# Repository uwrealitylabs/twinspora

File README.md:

# twin28xx

Twin DRV8316 motor drivers controlled by an STM32G473 with an onboard MT6701 magnetic encoder for each motor. Sized to fit two iPOWER GM2804 / Cubemars GL-30 motors on the back of the PCB.

## Specs

- **MCU:** STM32G473
- **Motor drivers:** 2× DRV8316CR (Controlled via SPI)
- **Encoder:** MT6701 onboard. Optional SPI breakout for remotely-mounted motors — desolder 3× 0603 resistors to disconnect onboard sensor & use "JST" SH-1.0 6 pin header.
- **Connectivity:** CAN-FD, USB 2.0, I²C

## Power & decoupling

- 2x B2B (BK22C07-4DP/2-0.4V) for power input + CAN. In the future there will be alternate versions with screw terminal & XT-30. 
- Reverse-polarity protection on the supply input
- 2× 330 µF electrolytic bulk caps
- 12× 0805 ceramic footprints (6 per driver) for additional decoupling

## Protection

- ESD protection on every external connector

## Configuration

- 2.54mm through hole headers for CAN bus termination and I²C pull-ups

Inspired by/references:
- microspora: https://oshwlab.com/the.skuric/microspora-simplefoc-antun
- Lemon Pepper Stepper: https://github.com/VIPQualityPost/lemon-pepper-stepper

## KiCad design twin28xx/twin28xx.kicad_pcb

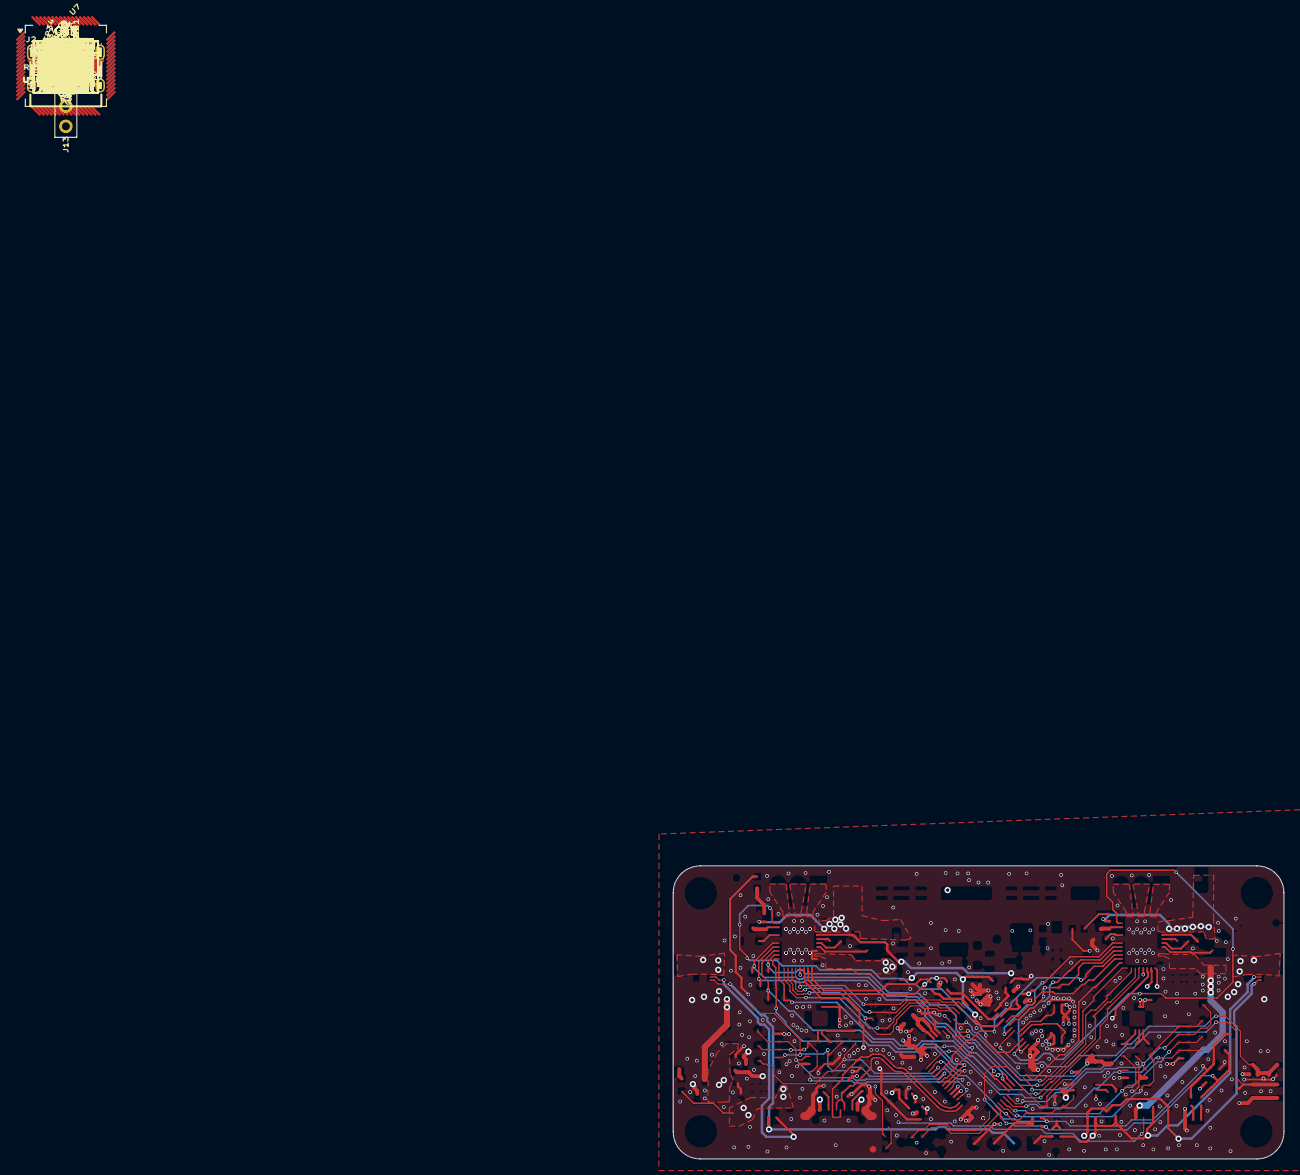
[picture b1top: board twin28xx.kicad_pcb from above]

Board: 4 copper layers, 76.9 x 36.9 mm, 201 parts (0 on the bottom side), 111 nets.

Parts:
C1, C2: 0402CG470J500NT; C_0402_1005Metric
C3, C4, C6, C16, C19, C20, C21, C22, C23, C25, C27, C36, C50, C59, C60: CL05B104KB54PNC; C_0402_1005Metric
C5, C26, C28, C29: CL05A105KA5NQNC; C_0402_1005Metric
C7, C8, C34, C35, C37, C48, C49, C51: GRM21BR61H106KE43L; C_0805_2012Metric
C9, C10, C12, C13, C15, C17, C30: CL05B103KB5NNNC; C_0402_1005Metric
C11, C18: 0402CG300J500NT; C_0402_1005Metric
C14, C24: CL10A475KO8NNNC; C_0603_1608Metric
C31, C33, C45, C47: CL10A105KB8NNNC; C_0603_1608Metric
C32, C46: CL10B473KB8NNNC; C_0603_1608Metric
C38, C39, C40, C41, C42, C43: VHXC0581V101MVCG; CP_Elec_6.3x5.8
D1, D2: 1N4148WS_T4; D_SOD-323_HandSoldering
D3, D4: BZT52B5V1S_C19077434; D_SOD-323_HandSoldering
FID1, FID2, FID3: Fiducial; Fiducial_0.5mm_Mask1mm
H1, H4, H7, H10: MountingHole_Pad; MountingHole_3.2mm_M3_Pad_Via
H2, H5, H8, H11: MountingHole_Pad; MountingHole_2.2mm_M2_DIN965_Pad
H3, H6, H9, H12: SMTSOM225BTR; SMD_BD5.6-D3.6
J1, J7, J8: XY-SH1_0-3A61; CONN-SMD_3P-P1.00_XYECONN_XY-SH1.0-3A61
J2: TYPE-C-31-M-12; USB-C_SMD-TYPE-C-31-M-12_1
J3: Tag-Connect_TC2030-IDC-NL_2x03_P1.27mm_Vertical
J4: DB125-2_54-2P-GN__mirror; CONN-TH_DB125-2.54-2P-GN__mirror
J5: XY-SH1_0-4A61; CONN-SMD_4P-P1.00_XYECONN_XY-SH1.0-4A61
J6: DB125-2_54-2P-GN; CONN-TH_DB125-2.54-2P-GN
J9, J10: Conn_01x03; CONN-TH_DB125-2.54-3P-GN
J11, J12: XY-SH1_0-6A51; CONN-SMD_6P-P1.00_XY-SH1.0-6A51
J13: Conn_01x04; PinHeader_1x04_P2.54mm_Vertical
L1, L2: PRS3015-470MT; IND-SMD_L3.0-W3.0_PRS3015
L3: GZ1608D601TF; L_0603_1608Metric
LED1, LED2: KT-0603W; LED0603-R-RD_WHITE
LED3, LED4, LED5: KT-0603R; LED0603-RD
Q1: AO3401A; SOT-23
R1, R4, R7, R11, R22, R26: 0402WGF1002TCE; R_0402_1005Metric
R2, R3, R5, R6, R18, R40: 0402WGF5101TCE; R_0402_1005Metric
R8, R9, R10, R30, R39: 0402WGF3300TCE; R_0402_1005Metric
R12, R13, R14, R17, R19, R20: 0402WGF499JTCE; R_0402_1005Metric
R15, R16, R21: 0402WGF1200TCE; R_0402_1005Metric
R23, R24, R31, R32, R33, R34, R36, R37, R38: 0603WAF0000T5E; R_0603_1608Metric
R25, R29, R35: 0402WGF1003TCE; R_0402_1005Metric
R27, R28: 0402WGF604JTCE; R_0402_1005Metric
SW1, SW2: SKSGPAE010; SW-SMD_SKSGAAE010
TP1, TP2, TP3, TP4, TP5, TP6, TP7, TP8, TP9, TP10, TP11, TP12, TP13, TP14, TP15, TP16, TP17, TP18, TP19, TP20, TP21, TP22, TP23, TP24, TP25, TP26, TP27, TP28, TP29, TP30, TP31, TP32, TP33, TP34, TP35, TP36, TP37, TP38, TP39, TP40, TP41, TP42, TP43, TP44, TP45, TP46: TestPoint_Pad_D1.0mm
U1, U2: BK22C07-4DP/2-0_4V(800); CONN-SMD_4P-P0.40_BAM04-08073-0414
U3: FMMT620TA; SOT-23-3_L2.9-W1.6-P1.90-LS2.8-BR
U4: WSD4066DN; DFN-8_L3.2-W3.1-P0.65-LS3.4-BL-EP
U5: SMF30A_C19077518; SOD-123FL_L2.7-W1.8-LS3.8
U6, U10, U17, U19: SRV05-4A; SOT-23-6
U7: STM32G473RBTx; LQFP-64_10x10mm_P0.5mm
U8: TPD1E10B06DPYR; DFN1006-2L-BI
U9: XC6206P332MR; SOT-23-3_L2.9-W1.6-P1.90-LS2.8-BR
U11: CA-IF1044VD-Q1; DFN-8_L3.0-W3.0-P0.65-BL-EP2.45
U12: ACT1210D-101-2P-TL00; FILTER-SMD_4P-L3.2-W2.5-BL_ACT1210D-101-2P-TL00
U13: PESD2CAN; SOT-23-3_L2.9-W1.3-P1.90-LS2.4-BR
U14, U15: DRV8316CRRGFR; VQFN-40_L7.0-W5.0-P0.50-BL-EP5.7
U16, U18: MT6701QT; QFN-16-1EP_3x3mm_P0.5mm_EP1.7x1.7mm
X1: X322512MSB4SI

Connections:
+3.3V: C6.2, C7.1, C8.1, C20.1, C21.1, C22.1, C23.1, C24.1, C59.2, C60.2, J5.2, J11.2, J12.2, J13.4, L3.2, LED2.1 (A), LED4.2 (A), LED5.2 (A), R7.2, R34.2, SW1.1, SW1.3, TP25.1 (1_1), U7.1 (VBAT), U7.16 (VDD), U7.32 (VDD), U7.48 (VDD), U7.64 (VDD), U9.3 (Vout), U10.5 (VP), U14.37 (VREF/ILIM), U15.37 (VREF/ILIM), U16.13 (VDD), U16.14 (MODE), U17.5 (VP), U18.13 (VDD), U18.14 (MODE), U19.5 (VP)
+5V: C4.2, C5.2, C14.2, C16.2, D2.1 (K), Q1.2 (S), TP26.1 (1_1), U8.2, U9.2 (Vin), U11.3 (VCC)
+BATT: D1.1 (K), J4.2, J6.2, U1.5, U1.6, U1.9, U1.10, U2.5, U2.6, U2.9, U2.10, U4.1 (S1), U4.3 (S2)
/5V_BKOUT: C34.1, C35.1, J1.2, L1.1, U14.3 (FB_BK)
/ADC1_IN3: C9.2, R12.1, U7.14 (PA2)
/ADC1_IN4: C13.2, R17.1, U7.17 (PA3)
/ADC2_IN1: C10.2, R13.1, U7.12 (PA0)
/ADC2_IN2: C15.2, R19.1, U7.13 (PA1)
/ADC5_IN1: C12.2, R14.1, U7.42 (PA8)
/ADC5_IN2: C17.2, R20.1, U7.43 (PA9)
/BOOT: R6.2, SW1.2, SW1.4, U7.61 (PB8)
/BUCK: C48.1, C49.1, L2.1, Q1.3 (D), TP45.1 (1_1), U15.3 (FB_BK)
/CAN_H: J7.3, J8.3, R21.2, R23.2, R28.2, U1.4, U2.4, U12.4, U13.1
/CAN_L: J7.2, J8.2, J13.2, R24.2, U1.3, U2.3, U12.3, U13.2
/CAN_VIO: C19.2, R22.2, TP43.1 (1_1), U7.22 (PC4), U11.5 (VIO/NC)
/CC1: J2.A5 (CC1), R2.1
/CC2: J2.B5 (CC2), R3.1
/D+: C2.2, J2.A6 (DP1), J2.B6 (DP2), U6.1 (IO1), U6.6 (IO4), U7.46 (PA12)
/D-: C1.2, J2.A7 (DN1), J2.B7 (DN2), U6.3 (IO2), U6.4 (IO3), U7.45 (PA11)
/FDCAN_RX: TP18.1 (1_1), U7.34 (PB12), U11.4 (RXD)
/FDCAN_TX: TP17.1 (1_1), U7.59 (PB6), U11.1 (TXD)
/GPIO1: R30.2, U7.3 (PC14), U14.22 (nFAULT)
/GPIO2: R39.2, U7.4 (PC15), U15.22 (nFAULT)
/GPIO3: J1.3, U7.26 (PB2)
/I2C_SCL: R16.2, R40.1, TP30.1 (1_1), U7.51 (PA15), U10.1 (IO1), U10.6 (IO4)
/I2C_SDA: R15.1, R18.1, TP29.1 (1_1), U7.60 (PB7), U10.3 (IO2), U10.4 (IO3)
/PHA1: J9.1, U14.13 (OUTA), U14.14 (OUTA)
/PHA2: J10.1, U15.13 (OUTA), U15.14 (OUTA)
/PHB1: J9.2, U14.16 (OUTB), U14.17 (OUTB)
/PHB2: J10.2, U15.16 (OUTB), U15.17 (OUTB)
/PHC1: J9.3, U14.19 (OUTC), U14.20 (OUTC)
/PHC2: J10.3, U15.19 (OUTC), U15.20 (OUTC)
/RCC_OSC_IN: C11.1, U7.5 (PF0), X1.1 (OSC1)
/RCC_OSC_OUT: C18.2, U7.6 (PF1), X1.3 (OSC2)
/RESET: C3.2, R7.1, SW2.1, SW2.3, U7.7 (PG10)
/SOA1: R12.2, TP19.1 (1_1), U14.40 (SOA)
/SOA2: R17.2, TP20.1 (1_1), U15.40 (SOA)
/SOB1: R13.2, TP21.1 (1_1), U14.39 (SOB)
/SOB2: R19.2, TP22.1 (1_1), U15.39 (SOB)
/SOC1: R14.2, TP23.1 (1_1), U14.38 (SOC)
/SOC2: R20.2, TP24.1 (1_1), U15.38 (SOC)
/SPI1_MISO: TP4.1 (1_1), U7.20 (PA6), U15.33 (SDO)
/SPI1_MOSI: TP3.1 (1_1), U7.21 (PA7), U15.34 (SDI)
/SPI1_NSS: TP1.1 (1_1), U7.18 (PA4), U15.36 (nSCS)
/SPI1_SCK: TP2.1 (1_1), U7.19 (PA5), U15.35 (SCLK)
/SPI2_MISO: J12.4, R36.1, TP8.1 (1_1), U7.44 (PA10), U19.6 (IO4)
/SPI2_MOSI: J12.3, TP7.1 (1_1), U7.37 (PB15), U19.4 (IO3)
/SPI2_NSS: J12.5, R37.1, TP5.1 (1_1), U7.41 (PC9), U19.3 (IO2)
/SPI2_SCK: J12.6, R38.1, TP6.1 (1_1), U7.35 (PB13), U19.1 (IO1)
/SPI3_MISO: J11.4, R33.1, TP12.1 (1_1), U7.53 (PC11), U17.6 (IO4)
/SPI3_MOSI: J11.3, TP11.1 (1_1), U7.54 (PC12), U17.4 (IO3)
/SPI3_NSS: J11.5, R32.1, TP9.1 (1_1), U7.55 (PD2), U17.3 (IO2)
/SPI3_SCK: J11.6, R31.1, TP10.1 (1_1), U7.52 (PC10), U17.1 (IO1)
/SPI4_MISO: TP16.1 (1_1), U7.24 (PB0), U14.33 (SDO)
/SPI4_MOSI: TP15.1 (1_1), U7.25 (PB1), U14.34 (SDI)
/SPI4_NSS: TP13.1 (1_1), U7.33 (PB11), U14.36 (nSCS)
/SPI4_SCK: TP14.1 (1_1), U7.30 (PB10), U14.35 (SCLK)
/SYS_SWCLK: J3.4, U7.50 (PA14)
/SYS_SWDIO: J3.2, U7.49 (PA13)
/TIM1_CH1: TP36.1 (1_1), U7.8 (PC0), U14.27 (INHA)
/TIM1_CH1N: TP35.1 (1_1), U7.2 (PC13), U14.28 (INLA)
/TIM1_CH2: TP34.1 (1_1), U7.9 (PC1), U14.29 (INHB)
/TIM1_CH2N: TP33.1 (1_1), U7.36 (PB14), U14.30 (INLB)
/TIM1_CH3: TP32.1 (1_1), U7.10 (PC2), U14.31 (INHC)
/TIM1_CH3N: TP31.1 (1_1), U7.62 (PB9), U14.32 (INLC)
/TIM8_CH1: TP42.1 (1_1), U7.38 (PC6), U15.27 (INHA)
/TIM8_CH1N: TP41.1 (1_1), U7.56 (PB3), U15.28 (INLA)
/TIM8_CH2: TP40.1 (1_1), U7.39 (PC7), U15.29 (INHB)
/TIM8_CH2N: TP39.1 (1_1), U7.57 (PB4), U15.30 (INLB)
/TIM8_CH3: TP38.1 (1_1), U7.40 (PC8), U15.31 (INHC)
/TIM8_CH3N: TP37.1 (1_1), U7.58 (PB5), U15.32 (INLC)
/USER_LED: LED3.2 (A), U7.23 (PC5)
/VCP: C47.2, R4.2, TP46.1 (1_1), U15.8 (CP)
/VDDA_DECOUPLE: C25.1, C26.1, C27.1, C28.1, L3.1, R34.1, U7.28 (VREF+), U7.29 (VDDA)
/VSENS: C29.2, R25.1, R26.2, TP28.1 (1_1), U7.11 (PC3)
/motor_driver/VCP: C33.2, U14.8 (CP)
GND: C1.1, C2.1, C3.1, C4.1, C5.1, C6.1, C7.2, C8.2, C9.1, C10.1, C11.2, C12.1, C13.1, C14.1, C15.1, C16.1, C17.1, C18.1, C19.1, C20.2, C21.2, C22.2, C23.2, C24.2, C25.2, C26.2, C27.2, C28.2, C29.1, C30.1, C31.1, C34.2, C35.2, C36.1, C37.1, C38.2, C39.2, C40.2, C41.2, C42.2, C43.2, C45.1, C48.2, C49.2, C50.1, C51.1, C59.1, C60.1, D3.2 (A), D4.2 (A), H1.1 (1_1), H2.1 (1_1), H3.1 (1_1), H4.1 (1_1), H5.1 (1_1), H6.1 (1_1), H7.1 (1_1), H8.1 (1_1), H9.1 (1_1), H10.1 (1_1), H11.1 (1_1), H12.1 (1_1), J1.1, J1.4, J1.5, J2.1 (EH), J2.2 (EH), J2.3 (EH), J2.4 (EH), J2.A1B12 (GND), J2.B1A12 (GND), J3.1, J4.1, J5.1, J5.5, J5.6, J6.1, J7.1, J7.4, J7.5, J8.1, J8.4, J8.5, J11.1, J11.7, J11.8, J12.1, J12.7, J12.8, R1.1, R2.2, R3.2, R5.2, R6.1, R8.2, R9.2, R11.1, R22.1, R26.1, SW1.5, SW1.6, SW2.2, SW2.4, SW2.5, SW2.6, TP27.1 (1_1), U1.7, U1.8, U1.11, U1.12, U2.7, U2.8, U2.11, U2.12, U5.2 (A), U6.2 (VN), U7.15 (VSS), U7.27 (VSSA), U7.31 (VSS), U7.47 (VSS), U7.63 (VSS), U8.1, U9.1 (GND), U10.2 (VN), U11.2 (GND), U11.8 (STB), U11.9 (EP), U13.3, U14.2 (AGND), U14.4 (GND_BK), U14.12 (PGND), U14.15 (PGND), U14.18 (PGND), U14.26 (AGND), U14.41 (PAD), U15.2 (AGND), U15.4 (GND_BK), U15.12 (PGND), U15.15 (PGND), U15.18 (PGND), U15.26 (AGND), U15.41 (PAD), U16.16 (GND), U16.17 (GND), U17.2 (VN), U18.16 (GND), U18.17 (GND), U19.2 (VN), X1.2 (GND), X1.4 (GND)
unnamed: C30.2, R27.2, R28.1
unnamed: D1.2 (A), U3.2 (E)
unnamed: D3.1 (K), R29.1, U14.23 (nSLEEP)
unnamed: D4.1 (K), R35.1, U15.23 (nSLEEP)
unnamed: J5.3, R15.2
unnamed: J5.4, R16.1
unnamed: J13.1, R21.1, R27.1
unnamed: J13.3, R18.2, R40.2
unnamed: LED1.2 (K), R5.1
unnamed: LED2.2 (K), R8.1
unnamed: LED3.1 (K), R9.1
unnamed: LED4.1 (K), R30.1
unnamed: LED5.1 (K), R39.1
unnamed: Q1.1 (G), R10.1, R11.2
unnamed: R1.2, U3.1 (B)
unnamed: R4.1, U3.3 (C), U4.2 (G1), U4.4 (G2)
unnamed: R23.1, U11.7 (CANH), U12.1
unnamed: R24.1, U11.6 (CANL), U12.2
unnamed: C31.2, U14.25 (AVDD)
unnamed: C32.2, U14.7 (CPH)
unnamed: C32.1, U14.6 (CPL)
unnamed: L1.2, U14.5 (SW_BK)
unnamed: C45.2, U15.25 (AVDD)
unnamed: C46.2, U15.7 (CPH)
unnamed: C46.1, U15.6 (CPL)
unnamed: L2.2, U15.5 (SW_BK)
unnamed: R33.2, U16.6 (A)
unnamed: R32.2, U16.7 (B)
unnamed: R31.2, U16.8 (Z)
unnamed: R36.2, U18.6 (A)
unnamed: R37.2, U18.7 (B)
unnamed: R38.2, U18.8 (Z)
VBUS: D2.2 (A), J2.A4B9 (VBUS), J2.B4A9 (VBUS), R10.2, U6.5 (VP)
VCC: C33.1, C36.2, C37.2, C38.1, C39.1, C40.1, C41.1, C42.1, C43.1, C47.1, C50.2, C51.2, LED1.1 (A), R25.2, R29.2, R35.2, TP44.1 (1_1), U4.5 (D2), U4.6 (D2), U4.7 (D1), U4.8 (D1), U4.9 (D1), U4.10 (D2), U5.1 (C), U14.9 (VM), U14.10 (VM), U14.11 (VM), U15.9 (VM), U15.10 (VM), U15.11 (VM)

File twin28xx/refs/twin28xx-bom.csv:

"Reference","Value","Footprint","LCSC","Description"
"C1,C2","0402CG470J500NT","Capacitor_SMD:C_0402_1005Metric","C1567","47pF ±5% 50V Ceramic Capacitor C0G 0402"
"C3,C4,C6,C16,C19-C23,C25,C27,C36,C50,C59,C60","CL05B104KB54PNC","Capacitor_SMD:C_0402_1005Metric","C307331","100nF ±10% 50V Ceramic Capacitor X7R 0402"
"C5,C26,C28,C29","CL05A105KA5NQNC","Capacitor_SMD:C_0402_1005Metric","C52923","1uF ±10% 25V Ceramic Capacitor X5R 0402"
"C7,C8,C34,C35,C37-C42,C48,C49,C51-C56","GRM21BR61H106KE43L","Capacitor_SMD:C_0805_2012Metric","C440198","10uF ±10% 50V Ceramic Capacitor X5R 0805"
"C9,C10,C12,C13,C15,C17,C30","CL05B103KB5NNNC","Capacitor_SMD:C_0402_1005Metric","C15195","10nF ±10% 50V Ceramic Capacitor X7R 0402"
"C11,C18","0402CG300J500NT","Capacitor_SMD:C_0402_1005Metric","C1570","30pF ±5% 50V Ceramic Capacitor C0G 0402"
"C14,C24","CL10A475KO8NNNC","Capacitor_SMD:C_0603_1608Metric","C19666","CAP CER 4.7uF 16V X5R 0603"
"C31,C33,C45,C47","CL10A105KB8NNNC","Capacitor_SMD:C_0603_1608Metric","C15849","1uF ±10% 50V Ceramic Capacitor X5R 0603"
"C32,C46","CL10B473KB8NNNC","Capacitor_SMD:C_0603_1608Metric","C1622","47nF ±10% 50V Ceramic Capacitor X7R 0603"
"C43,C57","EEEFT1H331GP","Capacitor_SMD_UWRL:CAP-SMD_BD10.0-L10.3-W10.3-LS11.0-R-RD","C542207",""
"C44,C58","50PX330MEFC10X16","Capacitor_THT_UWRL:CAP-TH_BD10.0-P5.00-D1.0-FD","C88789",""
"D1,D2","1N4148WS_T4","Diode_SMD:D_SOD-323_HandSoldering","C2128",""
"D3,D4","BZT52B5V1S_C19077434","Diode_SMD:D_SOD-323_HandSoldering","C19077434",""
"H3,H6,H9,H12","SMTSOM225BTR","Mechanical:SMD_BD5.6-D3.6","C5301773",""
"J1,J7,J8","XY-SH1_0-3A61","Connector_SH1.0:CONN-SMD_3P-P1.00_XYECONN_XY-SH1.0-3A61","C19271997",""
"J2","TYPE-C-31-M-12","Connector_USB:USB-C_SMD-TYPE-C-31-M-12_1","C165948",""
"J5","XY-SH1_0-4A61","Connector_SH1.0:CONN-SMD_4P-P1.00-WT","C19271998",""
"J9,J10","Conn_01x03","","","Generic connector, single row, 01x03, script generated (kicad-library-utils/schlib/autogen/connector/)"
"J11,J12","XY-SH1_0-6A51","Connector_SH1.0:CONN-SMD_6P-P1.00_XY-SH1.0-6A51","C19272009",""
"J13","Conn_01x04","Connector_PinHeader_2.54mm:PinHeader_1x04_P2.54mm_Vertical","","Generic connector, single row, 01x04, script generated (kicad-library-utils/schlib/autogen/connector/)"
"L1,L2","PRS3015-470MT","Inductor:IND-SMD_L3.0-W3.0_PRS3015","C96151",""
"L3,L4","BLM18PG121SN1D","Inductor_SMD:L_0603_1608Metric","C14709","120Ω@100MHz 700mA ferrite bead"
"LED1,LED2","KT-0603W","LED:LED0603-R-RD_WHITE","C2290",""
"LED3-LED5","KT-0603R","LED:LED0603-RD","C2286",""
"Q1","AO3401A","Package_TO_SOT_SMD:SOT-23","","-4.0A Id, -30V Vds, P-Channel MOSFET, SOT-23"
"R1,R4,R7,R11,R18,R22,R26","0402WGF1002TCE","Resistor_SMD:R_0402_1005Metric","C25744","10kΩ ±1% 62.5mW 0402 Thick Film Resistor"
"R2,R3,R5,R6","0402WGF5101TCE","Resistor_SMD:R_0402_1005Metric","C25905","5.1kΩ ±1% 62.5mW 0402 Thick Film Resistor"
"R8-R10,R30,R32","0402WGF3300TCE","Resistor_SMD:R_0402_1005Metric","C25104","RES 330Ω ±1% 62.5mW 0402"
"R12-R14,R17,R19,R20","0402WGF499JTCE","Resistor_SMD:R_0402_1005Metric","C25120","49.9Ω ±1% 62.5mW 0402 Thick Film Resistor"
"R15,R16,R21","0402WGF1200TCE","Resistor_SMD:R_0402_1005Metric","C25079","120Ω ±1% 62.5mW 0402 Thick Film Resistor"
"R23,R24,R33-R38","0603WAF0000T5E","Resistor_SMD:R_0603_1608Metric","C21189","0Ω ±1% 100mW 0603 Thick Film Resistor"
"R25,R29,R31","0402WGF1003TCE","Resistor_SMD:R_0402_1005Metric","C25741","100kΩ ±1% 62.5mW 0402 Thick Film Resistor"
"R27,R28","0402WGF604JTCE","Resistor_SMD:R_0402_1005Metric","C60310","RES 60.4Ω ±1% 62.5mW 0402"
"SW1,SW2","SKSGPAE010","Switch_UWRL:SW-SMD_SKSGAAE010","C125045",""
"U1,U2","BK22C07-4DP/2-0_4V(800)","Connector_HRS_BK22:CONN-SMD_4P-P0.40_BAM04-08073-0414","C27141223",""
"U3","FMMT620TA","Transistor_BJT_UWRL:SOT-23-3_L2.9-W1.6-P1.90-LS2.8-BR","C74081",""
"U4","WSD4066DN","Transistor_FET_UWRL:DFN-8_L3.2-W3.1-P0.65-LS3.4-BL-EP","C377861",""
"U5","SMF30CA_C19077519","Diode_UWRL:SOD-123FL_L2.7-W1.8-LS3.8-BI","C19077519",""
"U6,U10,U17,U19","SRV05-4A","Diode:SOT-23-6","","ESD Protection Diodes with Low Clamping Voltage, SOT-23-6"
"U7","STM32G473RBTx","Package_QFP:LQFP-64_10x10mm_P0.5mm","","STMicroelectronics Arm Cortex-M4 MCU, 128KB flash, 128KB RAM, 170 MHz, 1.71-3.6V, 52 GPIO, LQFP64"
"U8","H5VN10B","Diode_UWRL:DFN1006-2L-BI","C20615784",""
"U9","XC6206P332MR","Regulator_Linear:SOT-23-3_L2.9-W1.6-P1.90-LS2.8-BR","C5446",""
"U11","CA-IF1044VD-Q1","Interface_CAN_LIN:DFN-8_L3.0-W3.0-P0.65-BL-EP2.45","C5155979",""
"U12","ACT1210D-101-2P-TL00","CMC_UWRL:FILTER-SMD_4P-L3.2-W2.5-BL_ACT1210D-101-2P-TL00","C3039743",""
"U13","PESD2CAN","Diode_UWRL:SOT-23-3_L2.9-W1.3-P1.90-LS2.4-BR","C284078",""
"U14,U15","DRV8316CRRGFR","Motor_Driver:VQFN-40_L7.0-W5.0-P0.50-BL-EP5.7","C5447274",""
"U16,U18","MT6701QT","Package_DFN_QFN:QFN-16-1EP_3x3mm_P0.5mm_EP1.7x1.7mm","","Hall Based Angle Position Encoder Sensor, I2C, SSI, ABZ & UVW interfaces, 3.3..5V supply, QFN-16"
"X1","X322512MSB4SI","Oscillator:X322512MSB4SI","C9002","Crystal 12MHz ±10ppm 20pF SMD3225-4P"

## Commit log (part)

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2026-02-23 init
2026-02-23 chip add
    remaining components:
    C5447274 -- DRV8316CRRGFR
    C5155979 -- CA-IF1044VD-Q1
    C19077434 -- BZT52B5V1S
    C22459526 -- TS1187A26020
    C2875244 -- CJ15-160000810A20
2026-02-24 g473 labels
2026-02-24 schematic and library work
2026-02-24 push again
2026-02-25 finished schematic, added connectors
2026-02-26 new adc lpf values
2026-03-21 added smt nut
2026-04-19 initial completion
2026-04-19 designators
2026-04-19 final designator edits
2026-04-19 sum stitching vias
2026-04-19 metric hole spacing
2026-04-22 apr 21 push
2026-04-24 CAN wrong pinout
2026-04-24 more stitching vias
2026-04-29 fix shit
2026-04-30 caps and leds and fault
2026-05-04 b2b final
2026-05-04 fix readme
2026-05-04 small readme change
2026-05-05 MORE ESD
2026-05-06 split terminatino for can
2026-05-07 rear silkscreen
2026-05-07 new paths
2026-05-08 jlc time
2026-05-08 jlc 2
2026-05-18 ferrite bead
2026-05-18 fix silkscreen
2026-05-19 forgot the other i2c pullup
2026-05-19 pcb edits for the above
2026-05-22 latest
2026-05-27 move library submodule to repo root and switch to ../library path convention
    Relocate library submodule from twinspora/library to top-level library/ so
    projects sit alongside it (matches giris's layout). Update fp-lib-table,
    sym-lib-table, and twinspora.kicad_pcb to reference ${KIPRJMOD}/../library/
    instead of ${KIPRJMOD}/library/. Library submodule pointer bumped to 7a4a7dd
    which uses the same path convention internally for 3D model references.
